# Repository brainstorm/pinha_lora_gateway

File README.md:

# Mini-PCIe LoRa Gateway with PMOD and POE

This small LoRa gateway adapter (75x41mm) is motivated by the generous donation of a (n-fuse)[https://www.n-fuse.co/]'s LoRaWan [concentrator card](https://www.n-fuse.co/devices/LoRaWAN-Concentrator-Card-mini-PCIe.html). **This version of the board is meant to work with the USB firmware for the n-fuse board**:

Future versions might switch to the UART version of the n-fuse firmware.

RAK wireless boards might work with this adapter, but they are not tested... [I'm open to receive a RAKWireless board to try it out :)](https://twitter.com/RAKwireless/status/1138038732207087616?s=19).

The intention with this board is to have a maker-friendly LoRa gateway base design for modular gateways that incorporates the [PMOD flexibility](https://reference.digilentinc.com/_media/reference/pmod/pmod-interface-specification-1_2_0.pdf).

One could think it as a fusion of the following new developments (before they actually existed):

https://github.com/electroniceel/vocore2-breakout

https://m2m-tele.com/product/gw-01-poe/

# Software

There's the OpenWrt package that accompanies this work (and needs just a little bit more OSS love):

https://github.com/openwrt/packages/pull/8264

Which is pretty much a way to upstream the work shown by [Felix Wiedemann on hackster.io](https://www.hackster.io/fewi/build-a-lora-gateway-with-n-fuse-mpcie-card-71f0e1) with several UX improvements.

All in all, a neat experiment with 4 layer board design as a hobby while collaborating with a great company.

Thanks again n-fuse!

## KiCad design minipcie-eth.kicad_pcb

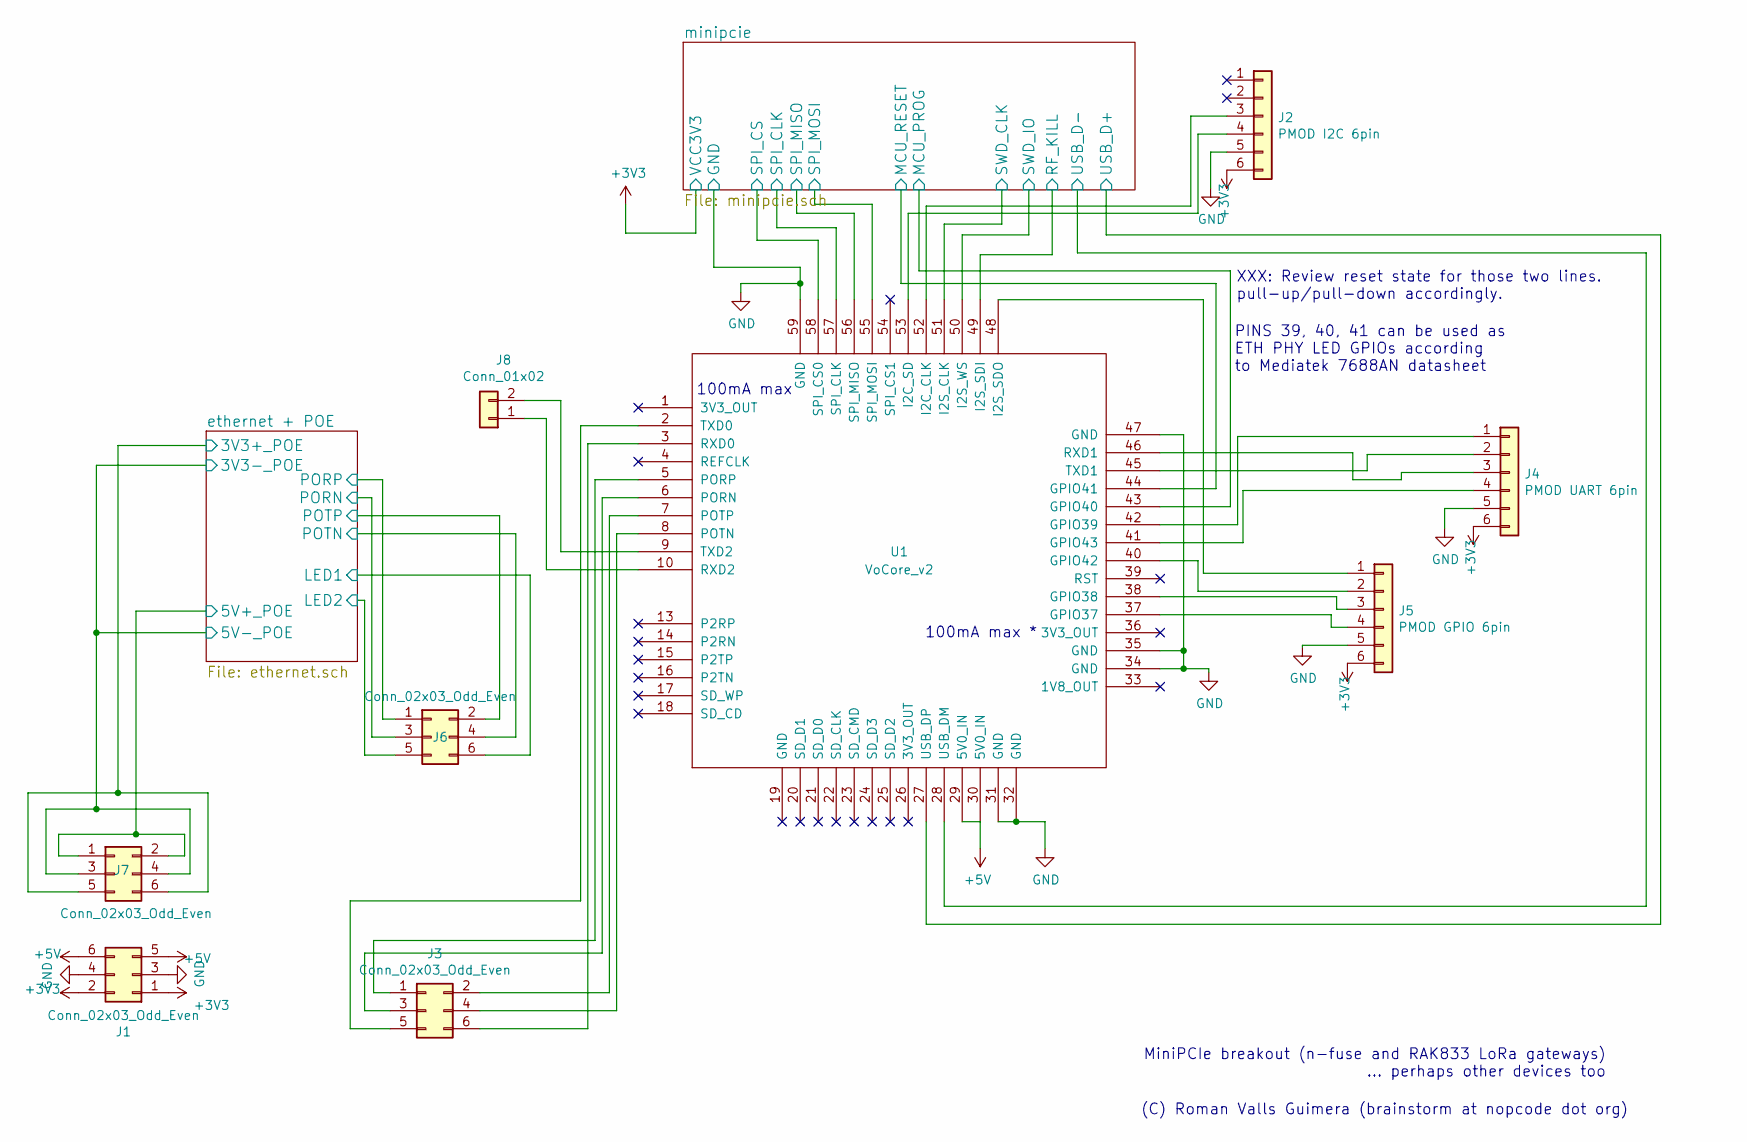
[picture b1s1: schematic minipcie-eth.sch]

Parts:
J1, J3: Conn_02x03_Odd_Even; PinHeader_2x03_P2.54mm_Vertical
J2: PMOD I2C 6pin; PinHeader_1x06_P2.54mm_Horizontal
J4: PMOD UART 6pin; PinHeader_1x06_P2.54mm_Horizontal
J5: PMOD GPIO 6pin; PinHeader_1x06_P2.54mm_Horizontal
J6, J7: Conn_02x03_Odd_Even; PinSocket_2x03_P2.54mm_Vertical
J8: Conn_01x02; PinHeader_1x02_P2.54mm_Vertical
U1: VoCore_v2; VOCORE2

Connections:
+3V3: J1.1, J1.2, J2.6, J4.6, J5.6; also elsewhere on the board
+5V: J1.5, J1.6, U1.29 (5V0_IN), U1.30 (5V0_IN)
/ethernet + POE/3V3+_POE: J7.5, J7.6; also elsewhere on the board
/ethernet + POE/3V3-_POE: J7.3, J7.4; also elsewhere on the board
/ethernet + POE/5V+_POE: J7.1, J7.2; also elsewhere on the board
/ethernet + POE/LED1: J6.6; also elsewhere on the board
/ethernet + POE/LED2: J6.5; also elsewhere on the board
/ethernet + POE/PORN: J6.3; also elsewhere on the board
/ethernet + POE/PORP: J6.1; also elsewhere on the board
/ethernet + POE/POTN: J6.4; also elsewhere on the board
/ethernet + POE/POTP: J6.2; also elsewhere on the board
/minipcie/MCU_PROG: U1.43 (GPIO40); also elsewhere on the board
/minipcie/MCU_RESET: U1.44 (GPIO41); also elsewhere on the board
/minipcie/RF_KILL: U1.49 (I2S_SDI); also elsewhere on the board
/minipcie/SPI_CLK: U1.57 (SPI_CLK); also elsewhere on the board
/minipcie/SPI_CS: U1.58 (SPI_CS0); also elsewhere on the board
/minipcie/SPI_MISO: U1.56 (SPI_MISO); also elsewhere on the board
/minipcie/SPI_MOSI: U1.55 (SPI_MOSI); also elsewhere on the board
/minipcie/SWD_CLK: U1.51 (I2S_CLK); also elsewhere on the board
/minipcie/SWD_IO: U1.50 (I2S_WS); also elsewhere on the board
/minipcie/USB_D+: U1.27 (USB_DP); also elsewhere on the board
/minipcie/USB_D-: U1.28 (USB_DM); also elsewhere on the board
GND: J1.3, J1.4, J2.5, J4.5, J5.5, U1.31 (GND), U1.32 (GND), U1.34 (GND), U1.35 (GND), U1.47 (GND), U1.59 (GND); also elsewhere on the board
unnamed: J2.3, U1.52 (I2C_CLK)
unnamed: J2.4, U1.53 (I2C_SD)
unnamed: J3.1, U1.5 (PORP)
unnamed: J3.2, U1.7 (POTP)
unnamed: J3.3, U1.6 (PORN)
unnamed: J3.4, U1.8 (POTN)
unnamed: J3.5, U1.2 (TXD0)
unnamed: J3.6, U1.3 (RXD0)
unnamed: J4.1, U1.42 (GPIO39)
unnamed: J4.2, U1.45 (TXD1)
unnamed: J4.3, U1.46 (RXD1)
unnamed: J4.4, U1.41 (GPIO43)
unnamed: J5.1, U1.48 (I2S_SDO)
unnamed: J5.2, U1.40 (GPIO42)
unnamed: J5.3, U1.38 (GPIO38)
unnamed: J5.4, U1.37 (GPIO37)
unnamed: J8.1, U1.10 (RXD2)
unnamed: J8.2, U1.9 (TXD2)

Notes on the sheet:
PINS 39, 40, 41 can be used as ETH PHY LED GPIOs according to Mediatek 7688AN datasheet
100mA max
MiniPCIe breakout (n-fuse and RAK833 LoRa gateways) … perhaps other devices too
100mA max *
XXX: Review reset state for those two lines. pull-up/pull-down accordingly.
(C) Roman Valls Guimera (brainstorm at nopcode dot org)

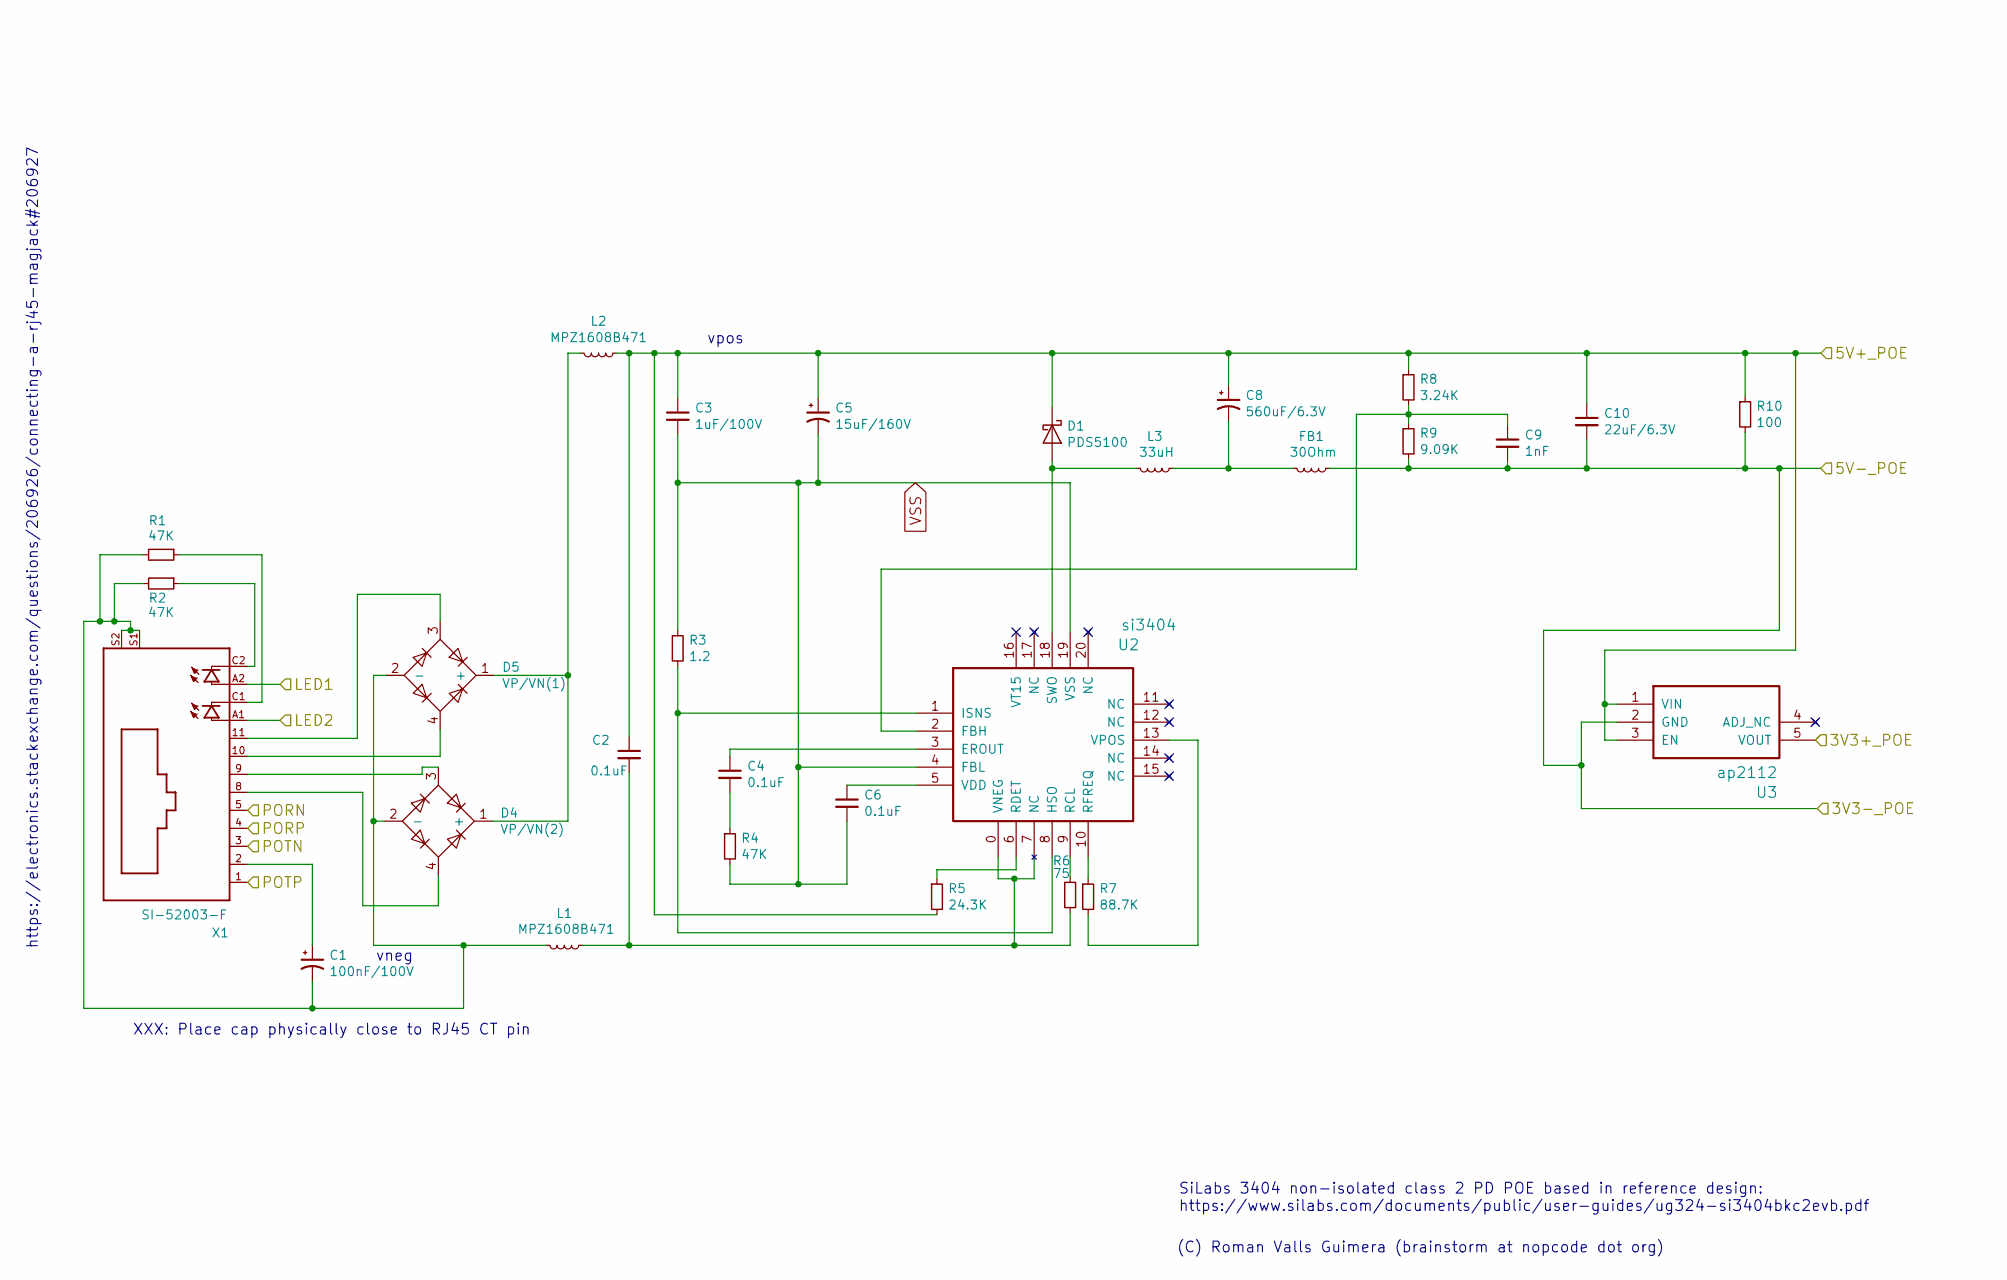
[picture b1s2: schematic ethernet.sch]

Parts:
C1: 100nF/100V; CP_Radial_D6.3mm_P2.50mm
C2, C4, C6: 0.1uF; C_0603
C3: 1uF/100V; C_1210
C5: 15uF/160V; CP_Radial_D6.3mm_P2.50mm
C8: 560uF/6.3V; CP_Radial_D8.0mm_P3.50mm
C9: 1nF; C_0603
C10: 22uF/6.3V; C_0603
D1: PDS5100; D_SMC
D4: VP/VN(2); Socket_Strip_Straight_2x02_Pitch2.00mm_SMD
D5: VP/VN(1); Socket_Strip_Straight_2x02_Pitch2.00mm_SMD
FB1: 30Ohm; L_1806
L1, L2: MPZ1608B471; L_1806
L3: 33uH; L_Neosid_SM-NE127
R1, R2, R4: 47K; R_0603
R3: 1.2; R_0603
R5: 24.3K; R_0603
R6: 75; R_0603
R7: 88.7K; R_0603
R8: 3.24K; R_0603
R9: 9.09K; R_0603
R10: 100; R_0603
U2: si3404; QFN-20-1EP_4x4mm_Pitch0.5mm
U3: ap2112; SOT-23-5
X1: SI-52003-F

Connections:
/ethernet + POE/3V3+_POE: U3.5 (VOUT); also elsewhere on the board
/ethernet + POE/3V3-_POE: C9.2, C10.2, FB1.1, R9.2, R10.2, U3.2 (GND); also elsewhere on the board
/ethernet + POE/5V+_POE: C2.1, C3.1, C5.1, C8.1, C10.1, D1.1 (K), L2.1, R5.2, R8.1, R10.1, U3.1 (VIN), U3.3 (EN); also elsewhere on the board
/ethernet + POE/LED1: X1.A2; also elsewhere on the board
/ethernet + POE/LED2: X1.A1; also elsewhere on the board
/ethernet + POE/PORN: X1.5 (RD-); also elsewhere on the board
/ethernet + POE/PORP: X1.4 (RD+); also elsewhere on the board
/ethernet + POE/POTN: X1.3 (TD-); also elsewhere on the board
/ethernet + POE/POTP: X1.1 (TD+); also elsewhere on the board
unnamed: C1.1, X1.2 (CT)
unnamed: C1.2, D4.2 (-), D5.2 (-), L1.2, R1.2, R2.2, X1.S1, X1.S2
unnamed: C2.2, L1.1, R6.2, U2.0 (VNEG), U2.7 (NC)
unnamed: C4.1, U2.3 (EROUT)
unnamed: C4.2, R4.1
unnamed: C6.1, U2.5 (VDD)
unnamed: C8.2, FB1.2, L3.1
unnamed: C9.1, R8.2, R9.1
unnamed: D1.2 (A), L3.2, U2.18 (SWO)
unnamed: D4.1 (+), D5.1 (+), L2.2
unnamed: D4.3, X1.9 (VC1-)
unnamed: D4.4, X1.8 (VC1+)
unnamed: D5.3, X1.11 (VC2-)
unnamed: D5.4, X1.10 (VC2+)
unnamed: R1.1, X1.C1
unnamed: R2.1, X1.C2
unnamed: R3.2, U2.1 (ISNS), U2.8 (HSO)
unnamed: R5.1, U2.6 (RDET)
unnamed: R6.1, U2.9 (RCL)
unnamed: R7.1, U2.10 (RFREQ)
unnamed: R7.2, U2.13 (VPOS)
VSS: C3.2, C5.2, C6.2, R3.1, R4.2, U2.4 (FBL), U2.19 (VSS)

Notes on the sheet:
https://electronics.stackexchange.com/questions/206926/connecting-a-rj45-magjack#206927
XXX: Place cap physically close to RJ45 CT pin
SiLabs 3404 non-isolated class 2 PD POE based in reference design: https://www.silabs.com/documents/public/user-guides/ug324-si3404bkc2evb.pdf
vneg
vpos
(C) Roman Valls Guimera (brainstorm at nopcode dot org)

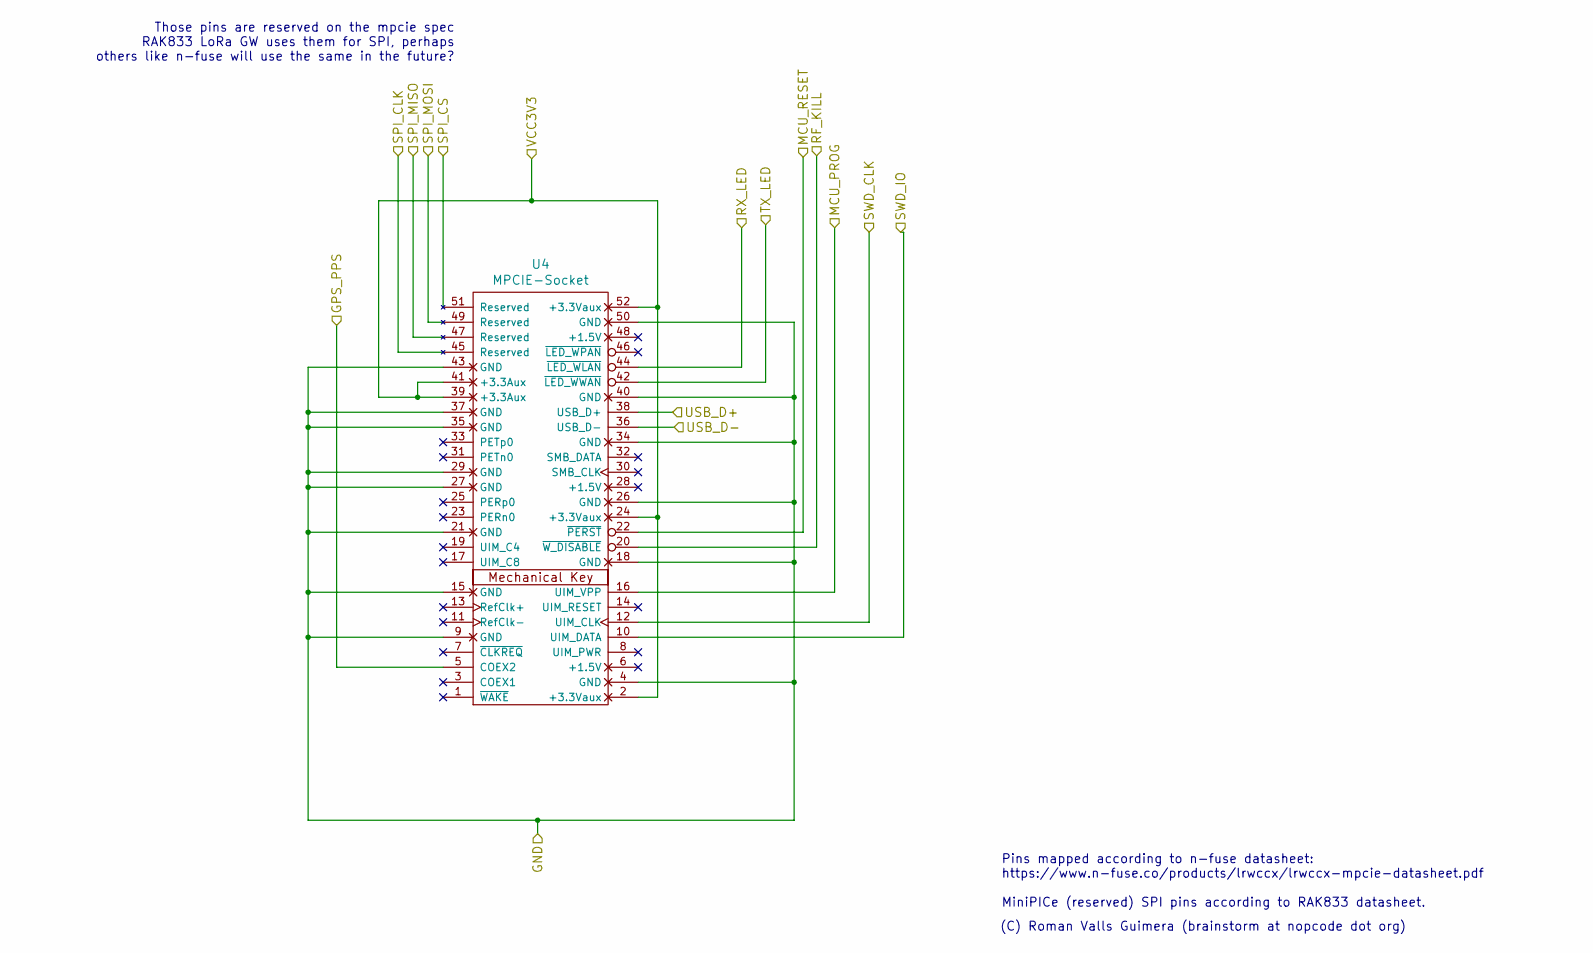
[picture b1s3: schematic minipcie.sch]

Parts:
U4: MPCIE-Socket; mpcie-socket

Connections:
+3V3: U4.2 (+3.3Vaux), U4.24 (+3.3Vaux), U4.39 (+3.3Aux), U4.41 (+3.3Aux), U4.52 (+3.3Vaux); also elsewhere on the board
/minipcie/MCU_PROG: U4.16 (UIM_VPP); also elsewhere on the board
/minipcie/MCU_RESET: U4.22 (~PERST); also elsewhere on the board
/minipcie/RF_KILL: U4.20 (~W_DISABLE); also elsewhere on the board
/minipcie/SPI_CLK: U4.45 (Reserved); also elsewhere on the board
/minipcie/SPI_CS: U4.51 (Reserved); also elsewhere on the board
/minipcie/SPI_MISO: U4.47 (Reserved); also elsewhere on the board
/minipcie/SPI_MOSI: U4.49 (Reserved); also elsewhere on the board
/minipcie/SWD_CLK: U4.12 (UIM_CLK); also elsewhere on the board
/minipcie/SWD_IO: U4.10 (UIM_DATA); also elsewhere on the board
/minipcie/USB_D+: U4.38 (USB_D+); also elsewhere on the board
/minipcie/USB_D-: U4.36 (USB_D-); also elsewhere on the board
GND: U4.4 (GND), U4.9 (GND), U4.15 (GND), U4.18 (GND), U4.21 (GND), U4.26 (GND), U4.27 (GND), U4.29 (GND), U4.34 (GND), U4.35 (GND), U4.37 (GND), U4.40 (GND), U4.43 (GND), U4.50 (GND); also elsewhere on the board

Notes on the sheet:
Pins mapped according to n-fuse datasheet: https://www.n-fuse.co/products/lrwccx/lrwccx-mpcie-datasheet.pdf MiniPICe (reserved) SPI pins according to RAK833 datasheet.
Those pins are reserved on the mpcie spec RAK833 LoRa GW uses them for SPI, perhaps others like n-fuse will use the same in the future?
(C) Roman Valls Guimera (brainstorm at nopcode dot org)

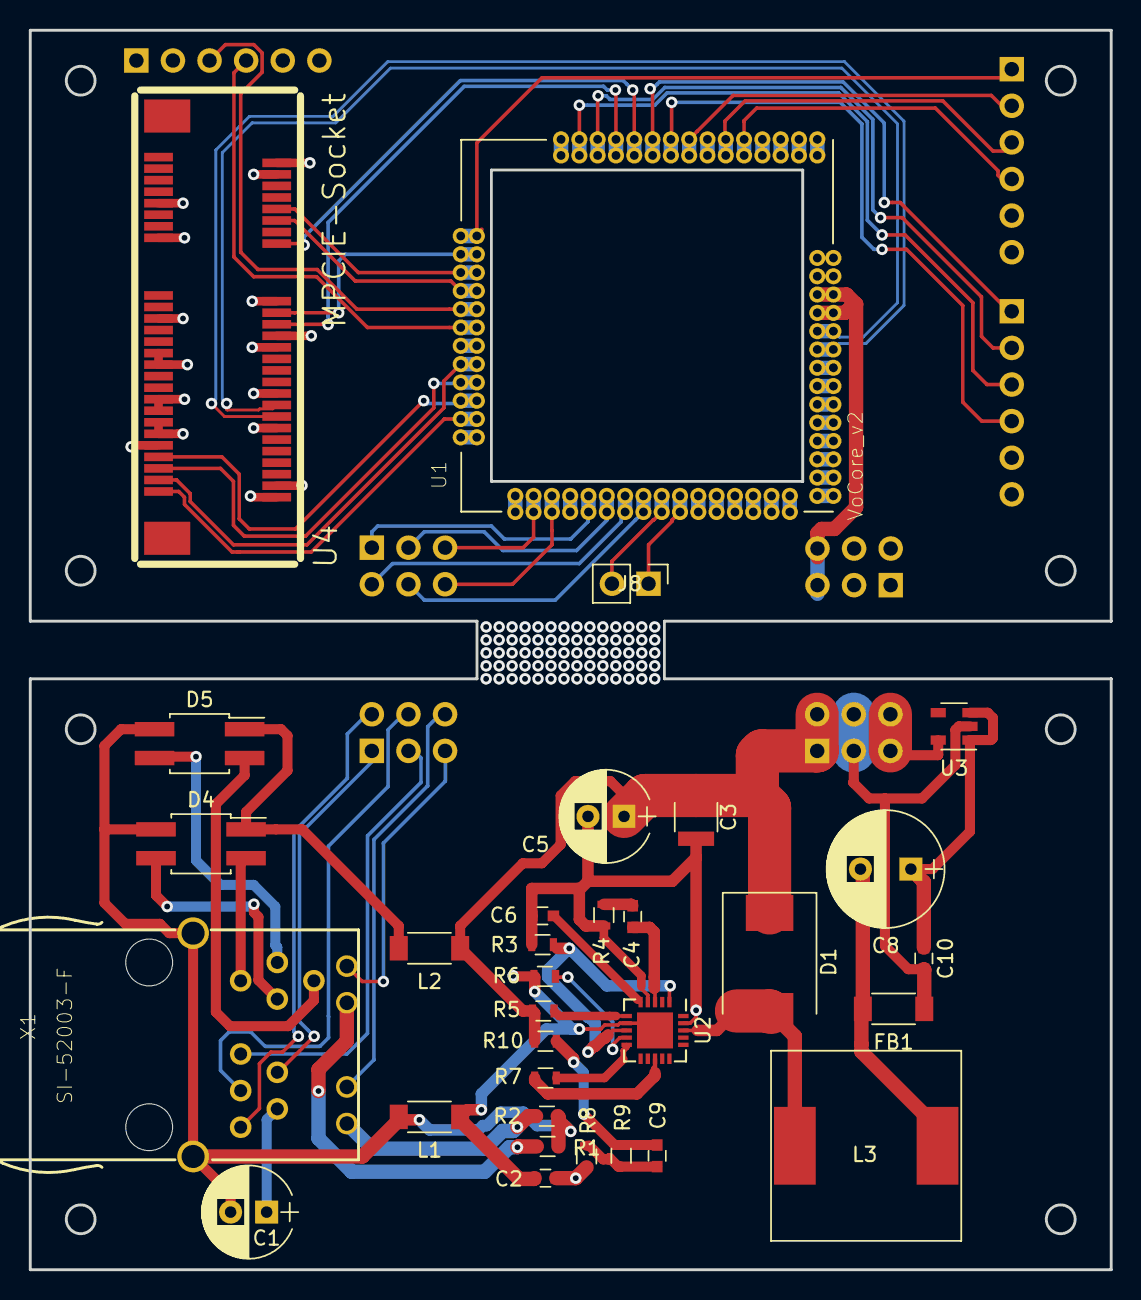
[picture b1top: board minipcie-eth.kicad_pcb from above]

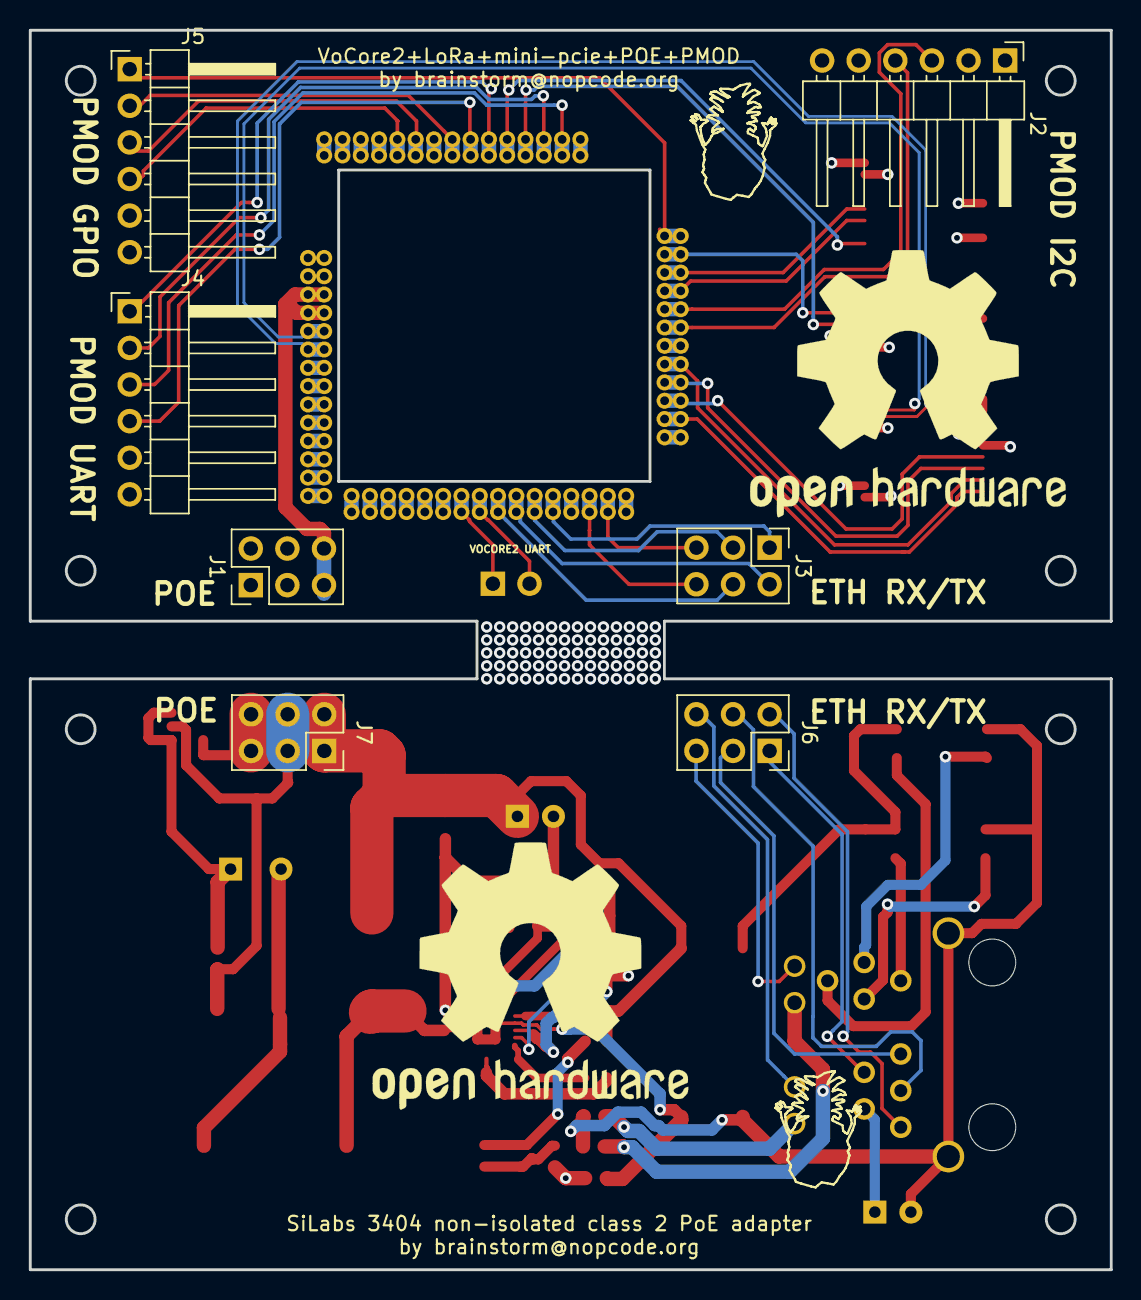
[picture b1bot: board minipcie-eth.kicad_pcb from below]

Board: 4 copper layers, 75.0 x 86.0 mm, 39 parts (7 on the bottom side), 63 nets.

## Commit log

2018-10-12 Initial commit, will go for si3406 for POE
2018-10-13 Add all POE logic with the si3404, schematic almost finished.
2018-10-14 Added SDcard wiring
2018-10-27 Rearrange components, validate package sizes, think about power plane placement since the ref design is 4 layers... can I add snubbers and other filtering and avoid 4-layer design?
2018-10-27 Correct main coil (from coilcraft) footprint
2018-10-28 Good discussion with Rob Powers about price margins for 2 layer PCB boards vs 4 layer PCBs... no market for that so closing this project and moving to a wESP32-based (or VoCore2) board :-S
2019-03-17 Migrate to KiCad 5.1 :)
2019-03-31 Migrate to board cuts/outline with hole for the VoCore
2019-04-20 Move libs away from rescue. Re-constrained board layout since cutouts were not perpendicular (overconstrained)
2019-04-20 Add snapeda vocore2 lib
2019-04-20 Mirrored board layout to accomodate the silabs companion board
2019-06-22 Added PMOD 6 header pins, mouse bites, copper fills for main board
2019-06-22 Initial 2-layer board routing proves unfeasible, switching to 4-layer design instead
2019-06-23 Mainboard routing finished with 4 layers. Status update sent to n-fuse
2019-07-14 Decided, I will switch to isolated si34061 design since the power budget and isolation are a bit too tight on the si3404... might change it all with the TPS23750 (https://www.ti.com/lit/ds/symlink/tp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
2019-07-14 No, go for si3404 first, the power budget is tight, but it can work and be significantly cheaper
2019-08-07 Switch to 90 degree orientation of the VoCore2. Separate 2.54mm pin headers into two 6-pin connectors, separating data and power, ready to re-route
2019-08-07 Add exported outlines
2019-08-10 Rearrangement to 90 degrees for the VoCore and routing complete. Fighting last 5 DRC violations and then on to double-checking dimensions and clearances
2019-08-10 Re-routed USB_D- renaming pads so that the differential router did not get confused with multiple pads with the same name. Also removed ghost tracks for USB_D- and RF Kill
2019-08-11 Routing finished, some of the si3404 application notes and via stitching ignored, to revisit later on
2019-08-14 Some fun with credits and logos
2019-08-14 Add README and some nice pictures
2019-08-14 Some minor final tweaks... holes for the standoffs for the minipci-e card are still missing :facepalm:
